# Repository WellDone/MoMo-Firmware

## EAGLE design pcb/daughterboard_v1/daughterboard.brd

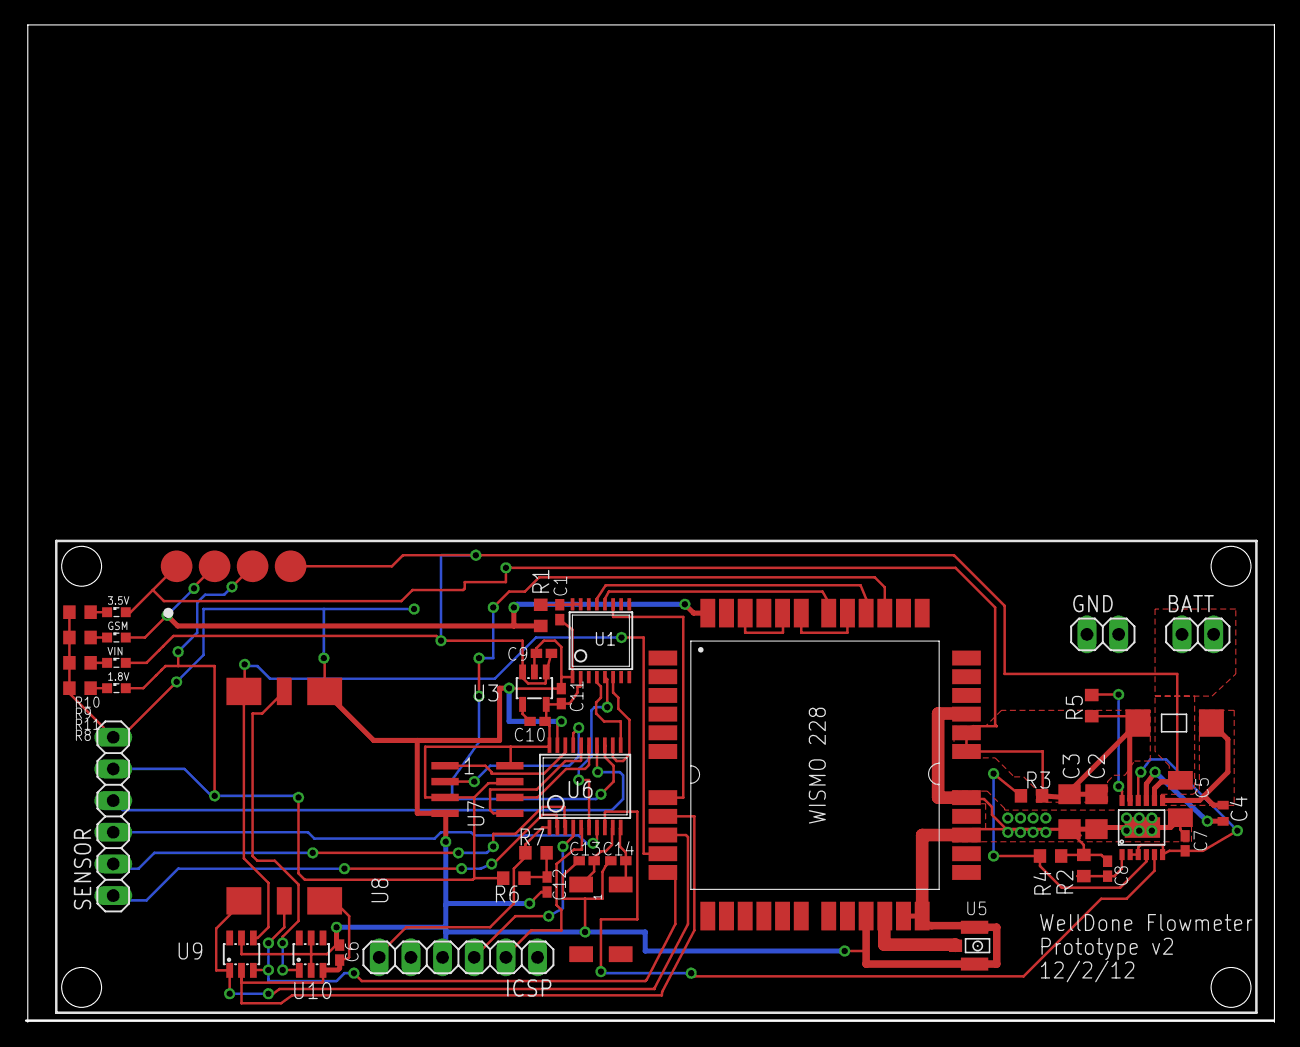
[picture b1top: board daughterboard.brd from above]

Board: 2 copper layers, 100.1 x 80.0 mm, 49 parts (0 on the bottom side), 47 nets.

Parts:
BATT: 1X02
C1: 1 nF; C0402K
C2, C3: 22 uF; C1206
C4: .1 uF; C0402
C5: 22 uF; C1206K
C6: 100 nF; C0402K
C7, C9, C11: 1 uF; C0402K
C8: .1 uF; C0402K
C10: 10 nF; C0402K
C12: .22 uF; C0402K
C13, C14: 3 pF; C0402K
GND: 1X02
ICSP: 1X06
L1: 3.3 uH; INDUCTORPROTO
LED1, LED2, LED3, LED4: SML0603
R1: 200 K; R0603
R2: 70K (1%); R0603
R3: 101K (1%); R0603
R4: 21K (1%); R0603
R5: 101K; R0603
R6: 10K; R0603
R7: 100; R0603
R8: 60; R0603
R9: 600; R0603
R10: 1K; R0603
R11: 2.7K; R0603
SENSOR: 1X06
TP1, TP2, TP3, TP4: TPB2,54; B2,54
U1: LEVELSHIFTER; TSSOP16
U2: LTC3600; MSOP12
U3: LT1761; SOT23-5L
U4: WISMO_228; GSM_MODULE
U5: RFANTENNA; RFJACK
U6: PIC24F16KA101-X_PSSOP; SSOP20
U7: FLASH8MSOP8; SOP08
U8: SIMSLOT
U9: DALC208; SOT23-6L
U10: ESDA6V1SC6; SOT23-6L
XTAL1: 32.768khz; SMDXTAL

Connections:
CLK: U4.SIM_CLK, U8.CLOCK, U9.1
CS: U6.18, U7.1
GND: C1.2, C2.2, C3.2, C5.2, C6.2, C7.2, C8.2, C9.2, C11.2, C12.2, C13.2, C14.2, GND.1, GND.2, ICSP.4, R2.1, R4.1, R8.1, R9.1, R10.1, R11.1, SENSOR.6, U1.1, U2.EXPOSED, U3.2, U4.GND, U4.GND1, U4.GND2, U4.GND3, U4.GND4, U4.GND5, U5.UNUSED1, U5.UNUSED2, U6.19, U7.4, U8.GND, U9.5, U10.2, U10.5
IO: U4.SIM_IO, U8.IO, U9.4
unnamed: U4.ANT, U5.ANTENNA
unnamed: C7.1, U2.PAD2, U2.PAD3, U2.PAD6, U2.PAD10
unnamed: U4.CT107/DSR, U4.CT108/DTR
unnamed: C1.1, R1.1, U1.15, U1.16
unnamed: U8.VPP, U10.1
unnamed: R3.1, R4.2, U2.PAD4
unnamed: LED1.C, R8.2
unnamed: LED2.C, R9.2
unnamed: C4.2, U2.PAD9
unnamed: C8.1, R2.2, U2.PAD1
unnamed: LED3.C, R10.2
unnamed: LED4.C, R11.2
unnamed: U2.PAD5, U6.8
unnamed: R5.1, U2.PAD12
unnamed: ICSP.2, U6.5
unnamed: ICSP.3, U6.4
unnamed: C10.2, U3.4
unnamed: C12.1, R6.1, R7.2
unnamed: ICSP.6, R7.1, U6.1
unnamed: U4.CT105/RTS, U4.CT106/CTS
unnamed: C14.1, U6.10, XTAL1.4
unnamed: C13.1, U6.9, XTAL1.1
unnamed: U1.13, U4.CT103/TXD
unnamed: U1.12, U4.CT104/RXD
unnamed: U1.11, U4.WISMO_READY
ON: U4.ON/OFF, U6.13
P0: SENSOR.1, U6.2
P1: SENSOR.2, U6.3
P2: SENSOR.3, U6.7
P3: SENSOR.4, U6.14
READY: U1.6, U6.12
RESET: U4.SIM_RST, U8.RESET, U9.3
RX: U1.5, U6.6
SCLK: U6.15, U7.6
SDI: U6.17, U7.2
SDO: U6.16, U7.5
SW: C4.1, L1.P1, U2.PAD7
TX: U1.4, U6.11
V+: BATT.1, BATT.2, C5.1, C9.1, LED4.A, TP4.TP, U2.PAD8, U3.1, U3.3
VCCINT: C10.1, C11.1, LED1.A, R6.2, SENSOR.5, TP1.TP, U1.2, U3.5, U6.20, U7.3, U7.7, U7.8
VCCIO: LED2.A, R1.2, TP2.TP, U4.VCC_2V8
VCCSIM: C6.1, U4.SIM_VCC, U8.VCC, U9.2, U10.3
VDD: C2.1, C3.1, L1.P2, LED3.A, R3.2, R5.2, TP3.TP, U2.PAD11, U4.VBAT1, U4.VBAT2

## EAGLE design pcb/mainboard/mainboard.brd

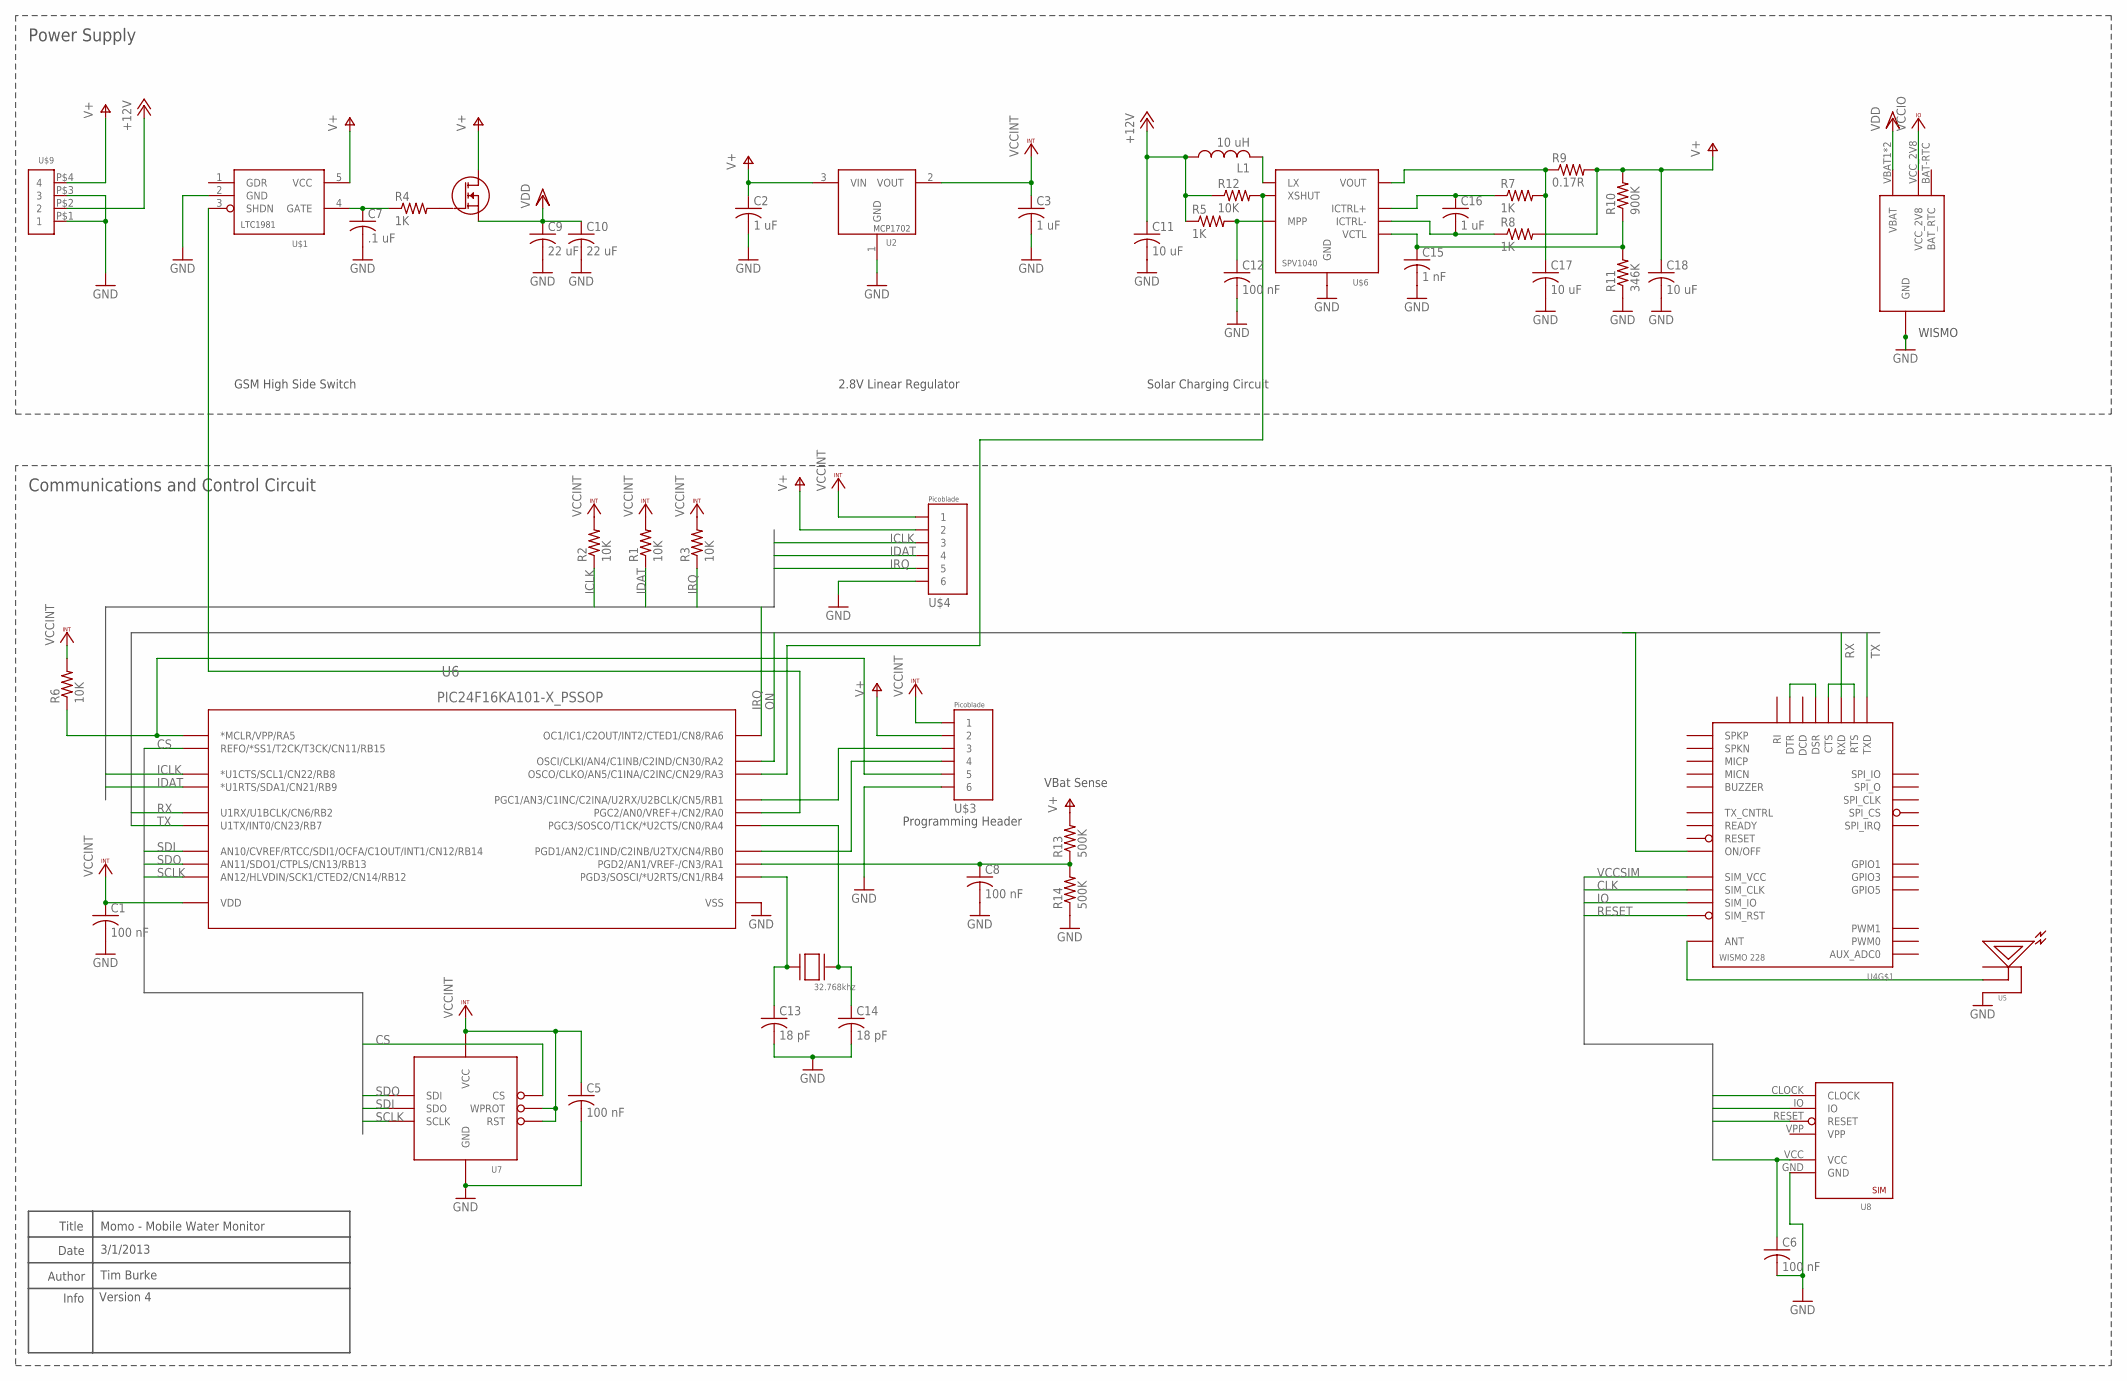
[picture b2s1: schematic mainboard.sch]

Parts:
C1, C5, C8, C12: 100 nF; C0402
C2, C3, C16: 1 uF; C0402
C6: 100 nF; C0402K
C7: .1 uF; C0402
C9, C10: 22 uF; C1206
C11, C17, C18: 10 uF; C0805
C13, C14: 18 pF; C0402K
C15: 1 nF; C0402
L1: 10 uH; L-COILCRAFT
R1, R2, R3, R6, R12: 10K; R0603
R4, R5, R7, R8: 1K; R0603
R9: 0.17R; R0805
R10: 900K; R0603
R11: 346K; R0603
R13, R14: 500K; R0603
U2: MCP1702; SOT23
U4: WISMO_228; GSM_MODULE
U5: RFANTENNA; RFJACK
U6: PIC24F16KA101-X_PSSOP; SSOP20
U7: FLASH8MSOP8; SOP08
U8: SIMSLOT
U$1: LTC1981; SOT23-5L
U$3, U$4: MICROCON6
U$5: N-MOSFET; SSOT-3
U$6: SPV1040; TSSOP8
U$9: SCREWTERM4
XTAL1: 32.768khz; 1206

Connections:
+12V: C11.1, L1.P$1 (1), R5.1, R12.1, U$9.P$2 (2)
CLK: U4.SIM_CLK, U8.CLOCK
CS: U6.18 (REFO/*SS1/T2CK/T3CK/CN11/RB15), U7.1 (CS)
GND: C1.2, C2.2, C3.2, C5.2, C6.2, C7.2, C8.2, C9.2, C10.2, C11.2, C12.2, C13.2, C14.2, C15.2, C17.2, C18.2, R11.1, R14.1, U2.1 (GND), U4.GND, U4.GND1 (GND), U4.GND2 (GND), U4.GND3 (GND), U4.GND4 (GND), U4.GND5 (GND), U5.UNUSED1 (SHIELD), U5.UNUSED2 (SHIELD), U6.19 (VSS), U7.4 (GND), U8.GND, U$1.2 (GND), U$3.6, U$4.6, U$6.2 (GND), U$9.P$1 (1), U$9.P$3 (3)
ICLK: R2.1, U6.12 (*U1CTS/SCL1/CN22/RB8), U$4.3
IDAT: R1.1, U6.13 (*U1RTS/SDA1/CN21/RB9), U$4.4
IO: U4.SIM_IO, U8.IO
IRQ: R3.1, U6.14 (OC1/IC1/C2OUT/INT2/CTED1/CN8/RA6), U$4.5
unnamed: U4.ANT, U5.ANTENNA (PIN)
unnamed: U4.CT107/DSR (DSR), U4.CT108/DTR (DTR)
unnamed: R4.2, U$5.1 (GATE)
unnamed: C12.1, R5.2, U$6.1 (MPP)
unnamed: C7.1, R4.1, U$1.4 (GATE)
unnamed: U6.2 (PGC2/AN0/VREF+/CN2/RA0), U$1.3 (SHDN)
unnamed: L1.P$2 (2), U$6.3 (LX)
unnamed: C15.1, R10.1, R11.2, U$6.5 (VCTL)
unnamed: C17.1, R7.2, R9.1, U$6.4 (VOUT)
unnamed: C16.1, R7.1, U$6.7 (ICTRL+)
unnamed: C16.2, R8.1, U$6.6 (ICTRL-)
unnamed: R12.2, U6.8 (OSCO/CLKO/AN5/C1INA/C2INC/CN29/RA3), U$6.8 (XSHUT)
unnamed: R6.1, U6.1 (*MCLR/VPP/RA5), U$3.5
unnamed: C8.1, R13.1, R14.2, U6.3 (PGD2/AN1/VREF-/CN3/RA1)
unnamed: U6.5 (PGC1/AN3/C1INC/C2INA/U2RX/U2BCLK/CN5/RB1), U$3.3
unnamed: U6.4 (PGD1/AN2/C1IND/C2INB/U2TX/CN4/RB0), U$3.4
unnamed: U4.CT105/RTS (RTS), U4.CT106/CTS (CTS)
unnamed: C14.1, U6.10 (PGC3/SOSCO/T1CK/*U2CTS/CN0/RA4), XTAL1.P$2 (XTAL2)
unnamed: C13.1, U6.9 (PGD3/SOSCI/*U2RTS/CN1/RB4), XTAL1.P$1 (XTAL1)
ON: U4.ON/OFF, U6.7 (OSCI/CLKI/AN4/C1INB/C2IND/CN30/RA2)
RESET: U4.SIM_RST, U8.RESET
RX: U4.CT104/RXD (RXD), U6.6 (U1RX/U1BCLK/CN6/RB2)
SCLK: U6.15 (AN12/HLVDIN/SCK1/CTED2/CN14/RB12), U7.6 (SCLK)
SDI: U6.17 (AN10/CVREF/RTCC/SDI1/OCFA/C1OUT/INT1/CN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), U7.2 (SDO)
SDO: U6.16 (AN11/SDO1/CTPLS/CN13/RB13), U7.5 (SDI)
TX: U4.CT103/TXD (TXD), U6.11 (U1TX/INT0/CN23/RB7)
V+: C2.1, C18.1, R8.2, R9.2, R10.2, R13.2, U2.3 (VIN), U$1.5 (VCC), U$3.2, U$4.2, U$5.3 (DRAIN), U$9.P$4 (4)
VCCINT: C1.1, C3.1, C5.1, R1.2, R2.2, R3.2, R6.2, U2.2 (VOUT), U6.20 (VDD), U7.3 (WPROT), U7.7 (RST), U7.8 (VCC), U$3.1, U$4.1
VCCIO: U4.VCC_2V8
VCCSIM: C6.1, U4.SIM_VCC, U8.VCC
VDD: C9.1, C10.1, U4.VBAT1 (VBAT), U4.VBAT2 (VBAT), U$5.2 (SOURCE)

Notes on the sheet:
WISMO
Programming Header
Communications and Control Circuit
Power Supply
GSM High Side Switch
2.8V Linear Regulator
Title
Author
Date
Momo - Mobile Water Monitor
3/1/2013
Tim Burke
Info
Version 4
Solar Charging Circuit
VBat Sense

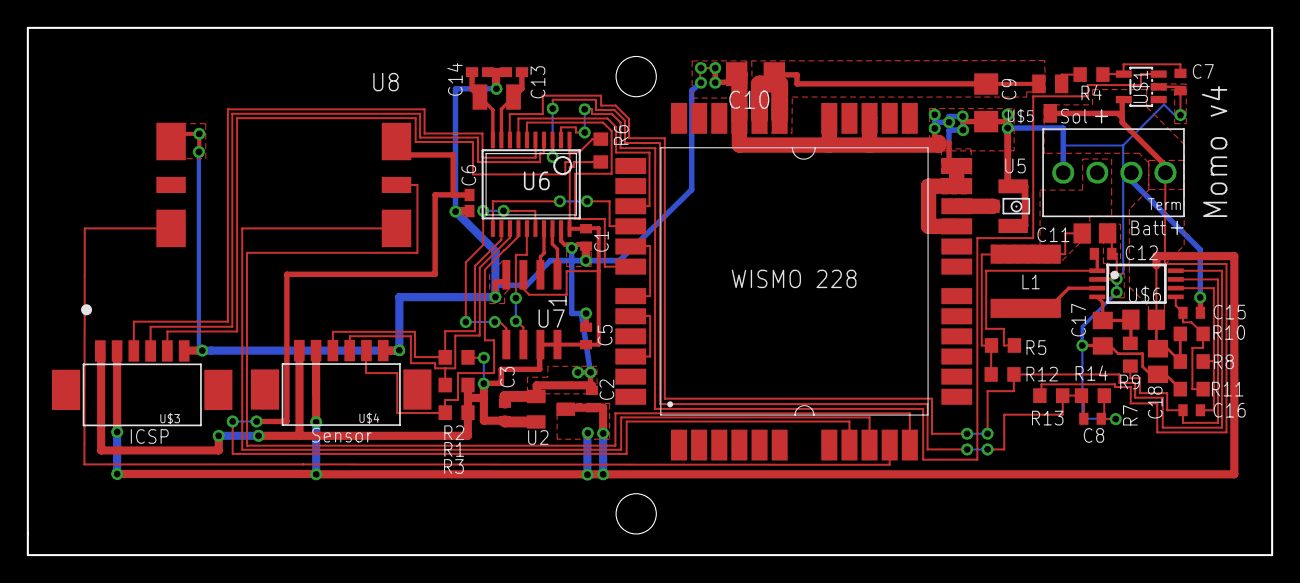
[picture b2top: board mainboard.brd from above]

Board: 2 copper layers, 92.7 x 39.3 mm, 45 parts (0 on the bottom side), 38 nets.

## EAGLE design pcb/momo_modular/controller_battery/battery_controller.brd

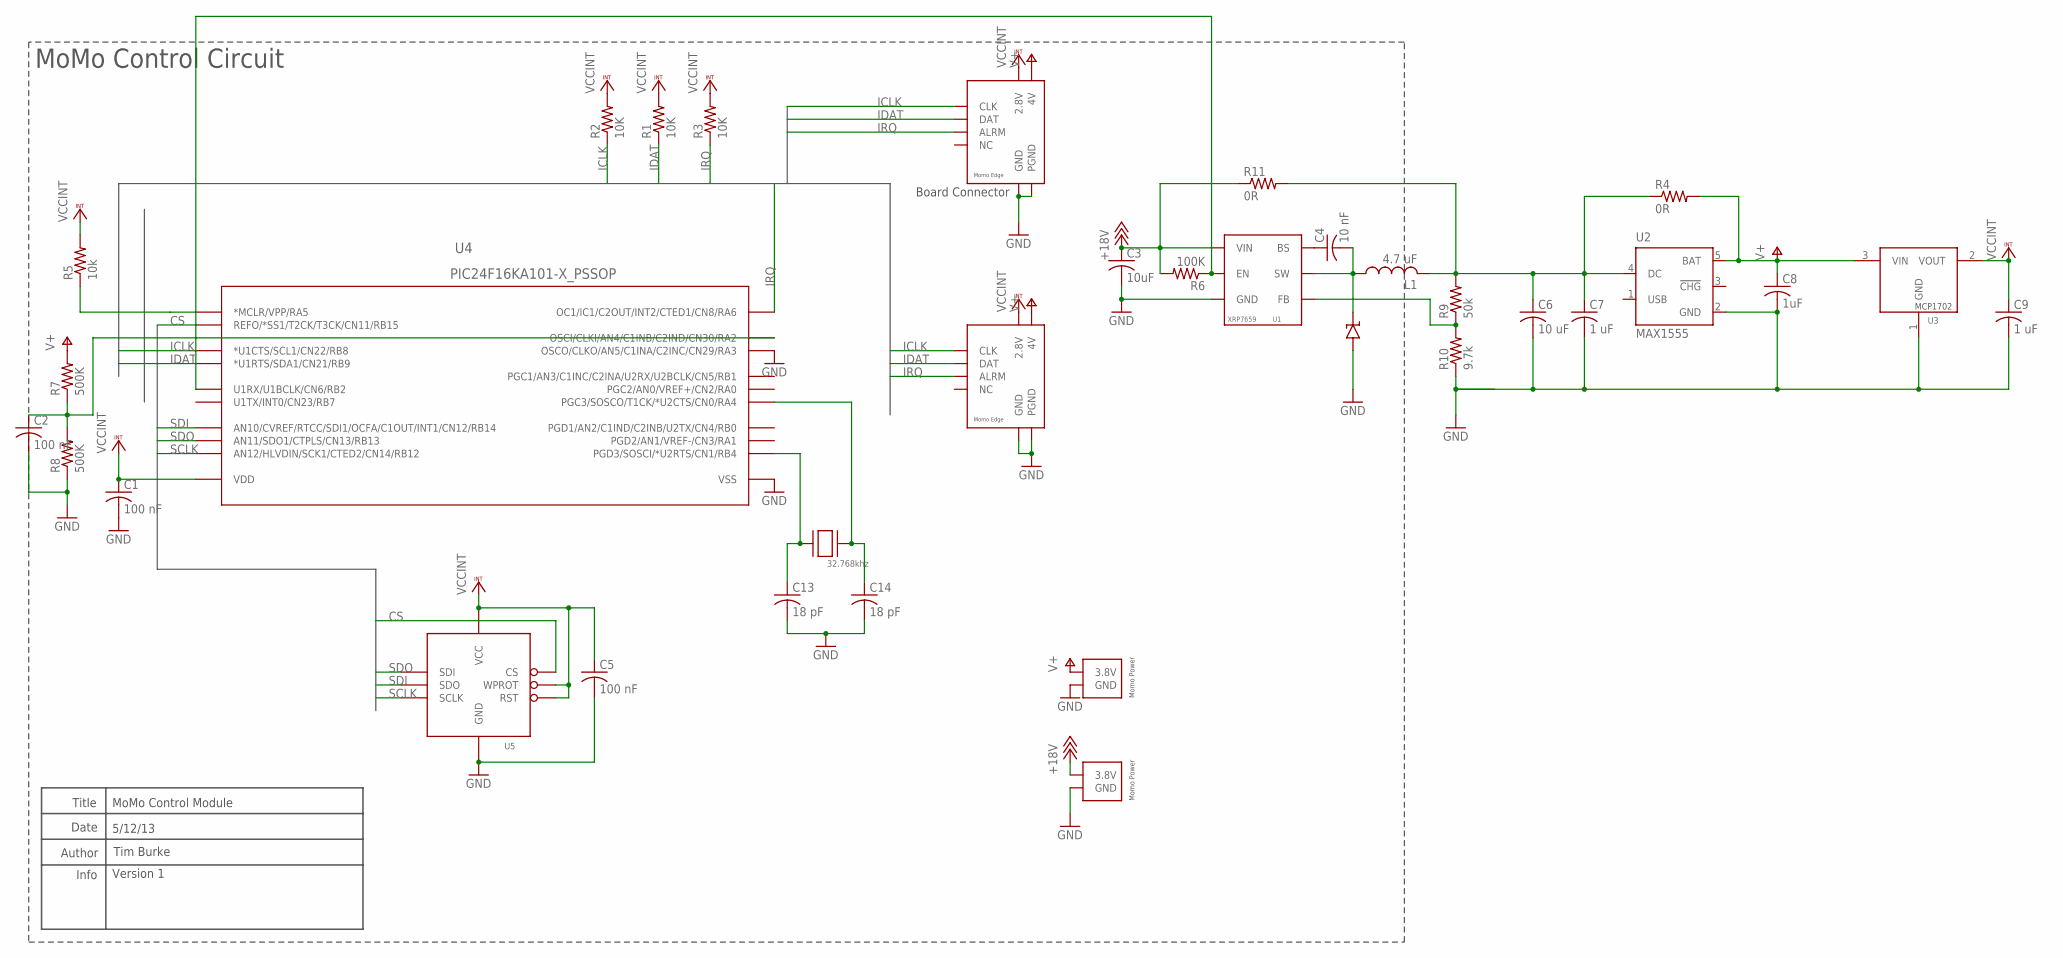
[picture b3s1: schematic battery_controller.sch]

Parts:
C1, C2, C5: 100 nF; C0402
C3: 10uF; C0805
C4: 10 nF; C0402
C6: 10 uF; C0805
C7, C9: 1 uF; C0402
C8: 1uF; C0402
C13, C14: 18 pF; C0402K
D1: DIODE_SS2P3SS2P3; DIODE_SS2P3
JP1: MOMO-VERT-8M; 1X08
JP3: MOMO-EDGE-8F
L1: 4.7 uF; NR6028-INDUCTOR
R1, R2, R3: 10K; R0603
R4, R11: 0R; R0603
R5: 10k; R0402
R6: 100K; R0603
R7, R8: 500K; R0603
R9: 50k; R0603
R10: 9.7k; R0603
U1: XRP7659; SOT23-6L
U2: MAX1555; SOT23-5L
U3: MCP1702; SOT23
U4: PIC24F16KA101-X_PSSOP; SSOP20
U5: FLASH8MSOP8; SOP08
U$1, U$2: MOMO-EDGE-POWER-M; MOMO-EDGE-SMALL-2M
XTAL1: 32.768khz; 1206

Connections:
+18V: C3.1, R6.2, R11.1, U1.5 (VIN), U$1.2 (3.8V)
CS: U4.18 (REFO/*SS1/T2CK/T3CK/CN11/RB15), U5.1 (CS)
GND: C1.2, C2.2, C3.2, C5.2, C6.2, C7.2, C8.2, C9.2, C13.2, C14.2, D1.AN, JP1.6 (GND), JP1.8 (PGND), JP3.GND, JP3.PGND, R8.1, R10.1, U1.2 (GND), U2.2 (GND), U3.1 (GND), U4.8 (OSCO/CLKO/AN5/C1INA/C2INC/CN29/RA3), U4.19 (VSS), U5.4 (GND), U$1.1 (GND), U$2.1 (GND)
ICLK: JP1.3 (CLK), JP3.CLK, R2.1, U4.12 (*U1CTS/SCL1/CN22/RB8)
IDAT: JP1.4 (DAT), JP3.DAT, R1.1, U4.13 (*U1RTS/SDA1/CN21/RB9)
IRQ: JP1.5 (ALRM), JP3.ARLM (ALRM), R3.1, U4.14 (OC1/IC1/C2OUT/INT2/CTED1/CN8/RA6)
unnamed: C6.1, C7.1, L1.2, R4.1, R9.2, R11.2, U2.4 (DC)
unnamed: C2.1, R7.1, R8.2, U4.7 (OSCI/CLKI/AN4/C1INB/C2IND/CN30/RA2)
unnamed: R6.1, U1.4 (EN), U4.6 (U1RX/U1BCLK/CN6/RB2)
unnamed: R9.1, R10.2, U1.3 (FB)
unnamed: C4.1, U1.1 (BS)
unnamed: C4.2, D1.CATH, L1.1, U1.6 (SW)
unnamed: R5.1, U4.1 (*MCLR/VPP/RA5)
unnamed: C14.1, U4.10 (PGC3/SOSCO/T1CK/*U2CTS/CN0/RA4), XTAL1.P$2 (XTAL2)
unnamed: C13.1, U4.9 (PGD3/SOSCI/*U2RTS/CN1/RB4), XTAL1.P$1 (XTAL1)
SCLK: U4.15 (AN12/HLVDIN/SCK1/CTED2/CN14/RB12), U5.6 (SCLK)
SDI: U4.17 (AN10/CVREF/RTCC/SDI1/OCFA/C1OUT/INT1/CN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), U5.2 (SDO)
SDO: U4.16 (AN11/SDO1/CTPLS/CN13/RB13), U5.5 (SDI)
V+: C8.1, JP1.7 (4V), JP3.V4. (4V), R4.2, R7.2, U2.5 (BAT), U3.3 (VIN), U$2.2 (3.8V)
VCCINT: C1.1, C5.1, C9.1, JP1.1 (2.8V), JP3.V28 (2.8V), R1.2, R2.2, R3.2, R5.2, U3.2 (VOUT), U4.20 (VDD), U5.3 (WPROT), U5.7 (RST), U5.8 (VCC)

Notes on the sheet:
Title
Author
Date
Tim Burke
Info
Board Connector
MoMo Control Module
Version 1
5/12/13
MoMo Control Circuit

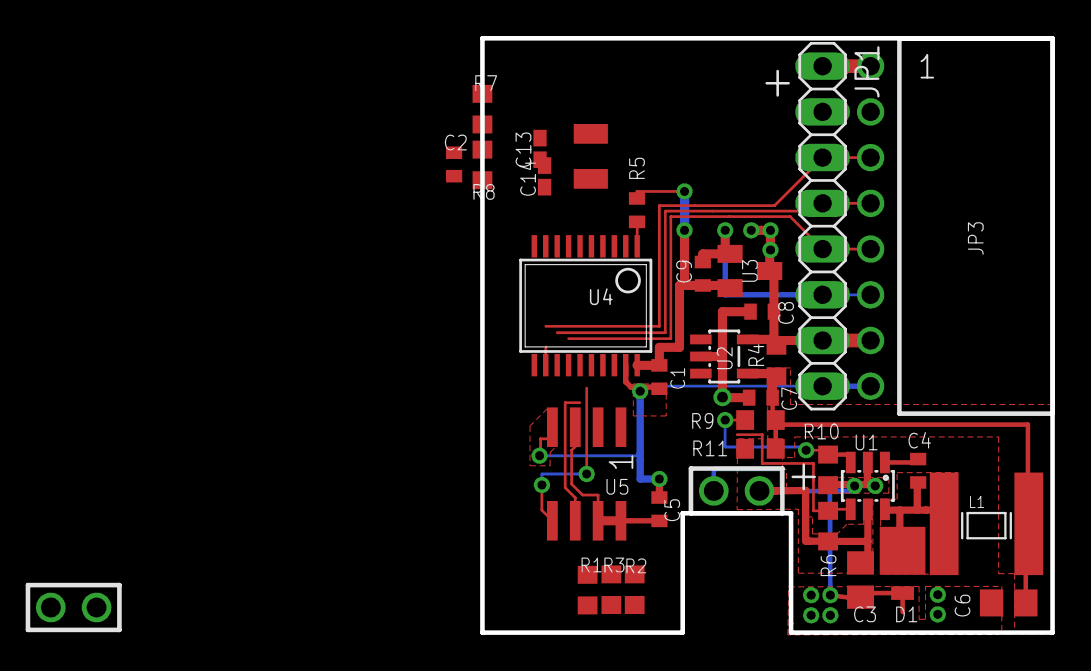
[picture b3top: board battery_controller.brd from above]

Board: 2 copper layers, 31.7 x 33.0 mm, 34 parts (0 on the bottom side), 20 nets.

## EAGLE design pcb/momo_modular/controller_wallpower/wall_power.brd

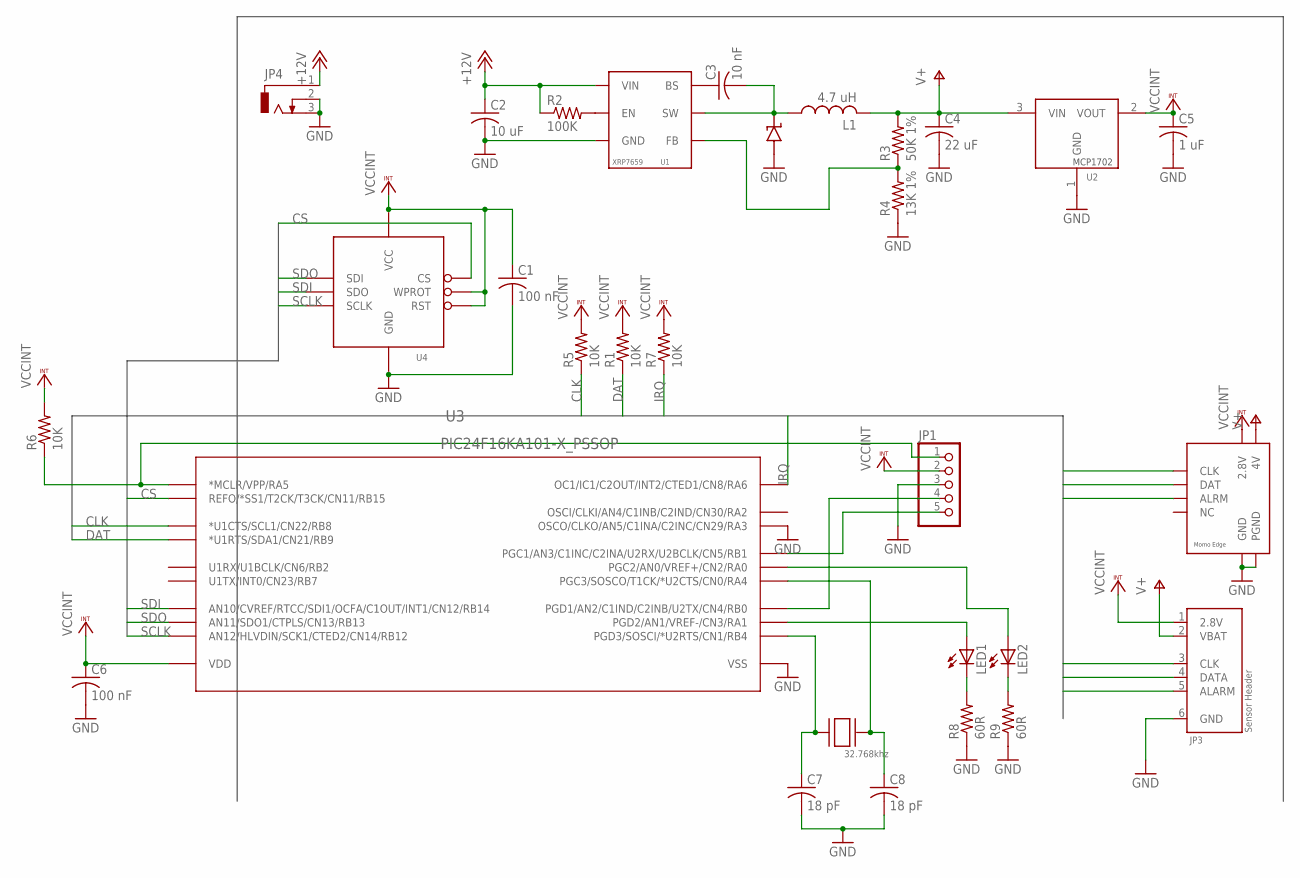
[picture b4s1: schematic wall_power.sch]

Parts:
C1, C6: 100 nF; C0402
C2: 10 uF; C0805
C3: 10 nF; C0402
C4: 22 uF; C1206
C5: 1 uF; C0402
C7, C8: 18 pF; C0402K
D1: DIODE_SS2P3SS2P3; DIODE_SS2P3
JP1: PINHD-1X5; 1X05
JP2: MOMO-EDGE-8F
JP3: MOMO-SENSOR-HEADER; 2X3-MOLEX-90130
JP4: DCJ0303
L1: 4.7 uH; NR6028-INDUCTOR
LED1, LED2: LEDSML0603; SML0603
R1, R5, R6, R7: 10K; R0603
R2: 100K; R0603
R3: 50K 1%; R0603
R4: 13K 1%; R0603
R8, R9: 60R; R0603
U1: XRP7659; SOT23-6L
U2: MCP1702; SOT23
U3: PIC24F16KA101-X_PSSOP; SSOP20
U4: FLASH8MSOP8; SOP08
XTAL1: 32.768khz; 1206

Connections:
+12V: C2.1, JP4.1, R2.1, U1.5 (VIN)
CLK: JP2.CLK, JP3.3 (CLK), R5.1, U3.12 (*U1CTS/SCL1/CN22/RB8)
CS: U3.18 (REFO/*SS1/T2CK/T3CK/CN11/RB15), U4.1 (CS)
DAT: JP2.DAT, JP3.4 (DATA), R1.1, U3.13 (*U1RTS/SDA1/CN21/RB9)
GND: C1.2, C2.2, C4.2, C5.2, C6.2, C7.2, C8.2, D1.AN, JP1.3, JP2.GND, JP2.PGND, JP3.6 (GND), JP4.2, JP4.3, R4.1, R8.1, R9.1, U1.2 (GND), U2.1 (GND), U3.8 (OSCO/CLKO/AN5/C1INA/C2INC/CN29/RA3), U3.19 (VSS), U4.4 (GND)
IRQ: JP2.ARLM (ALRM), JP3.5 (ALARM), R7.1, U3.14 (OC1/IC1/C2OUT/INT2/CTED1/CN8/RA6)
unnamed: LED2.A, U3.2 (PGC2/AN0/VREF+/CN2/RA0)
unnamed: C3.2, D1.CATH, L1.1, U1.6 (SW)
unnamed: R2.2, U1.4 (EN)
unnamed: C3.1, U1.1 (BS)
unnamed: LED2.C, R9.2
unnamed: R3.1, R4.2, U1.3 (FB)
unnamed: LED1.C, R8.2
unnamed: LED1.A, U3.3 (PGD2/AN1/VREF-/CN3/RA1)
unnamed: JP1.4, U3.4 (PGD1/AN2/C1IND/C2INB/U2TX/CN4/RB0)
unnamed: JP1.5, U3.5 (PGC1/AN3/C1INC/C2INA/U2RX/U2BCLK/CN5/RB1)
unnamed: JP1.1, R6.1, U3.1 (*MCLR/VPP/RA5)
unnamed: C8.1, U3.10 (PGC3/SOSCO/T1CK/*U2CTS/CN0/RA4), XTAL1.P$2 (XTAL2)
unnamed: C7.1, U3.9 (PGD3/SOSCI/*U2RTS/CN1/RB4), XTAL1.P$1 (XTAL1)
SCLK: U3.15 (AN12/HLVDIN/SCK1/CTED2/CN14/RB12), U4.6 (SCLK)
SDI: U3.17 (AN10/CVREF/RTCC/SDI1/OCFA/C1OUT/INT1/CN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), U4.2 (SDO)
SDO: U3.16 (AN11/SDO1/CTPLS/CN13/RB13), U4.5 (SDI)
V+: C4.1, JP2.V4. (4V), JP3.2 (VBAT), L1.2, R3.2, U2.3 (VIN)
VCCINT: C1.1, C5.1, C6.1, JP1.2, JP2.V28 (2.8V), JP3.1 (2.8V), R1.2, R5.2, R6.2, R7.2, U2.2 (VOUT), U3.20 (VDD), U4.3 (WPROT), U4.7 (RST), U4.8 (VCC)

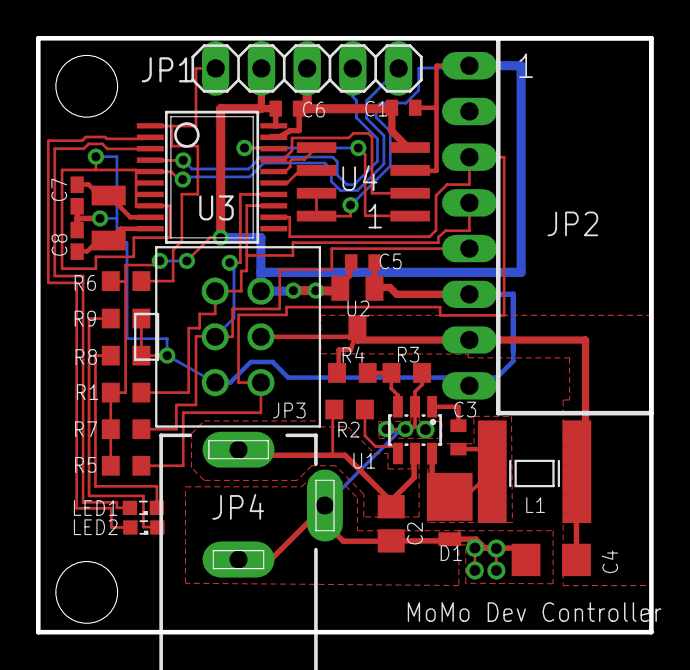
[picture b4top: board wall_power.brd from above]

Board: 2 copper layers, 34.1 x 33.0 mm, 30 parts (0 on the bottom side), 24 nets.

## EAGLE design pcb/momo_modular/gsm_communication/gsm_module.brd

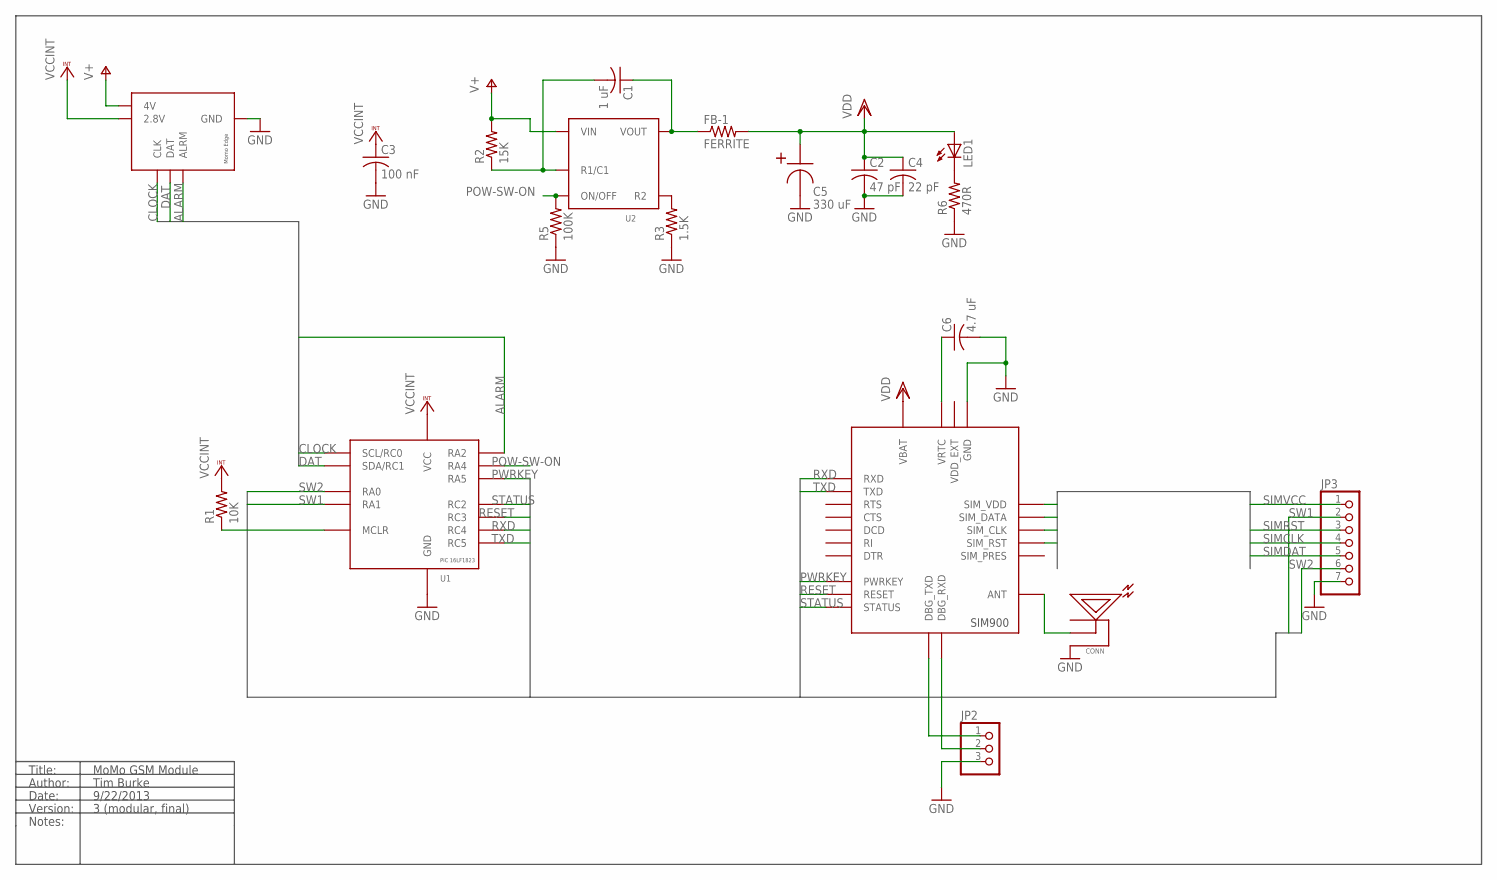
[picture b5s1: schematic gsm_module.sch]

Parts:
C1: 1 uF; C0402K; DIGIKEY-PN 445-4114-1-ND
C2: 47 pF; C0402K; DIGIKEY-PN 445-1243-1-ND
C3: 100 nF; C0402; DIGIKEY-PN 445-1265-1-ND
C4: 22 pF; C0402K; DIGIKEY-PN 445-1239-1-ND
C5: 330 uF; 2917
C6: 4.7 uF; C0805; DIGIKEY-PN 1276-1259-1-ND
CONN: RFANTENNA; RFJACK; DIGIKEY-PN J983CT-ND
FB-1: FERRITE; R0805; DIGIKEY-PN 445-1567-1-ND
JP1: MOMO-EDGE-6M
JP2: PINHD-1X3; 1X03
JP3: PINHD-1X7; 1X07
LED1: LEDCHIPLED_0603; CHIPLED_0603; DIGIKEY-PN 475-2709-1-ND
R1: 10K; R0603; DIGIKEY-PN P10.0KHCT-ND
R2: 15K; R0603; DIGIKEY-PN P15KGCT-ND
R3: 1.5K; R0603; DIGIKEY-PN P1.5KGCT-ND
R5: 100K; R0603; DIGIKEY-PN P100KHCT-ND
R6: 470R; R0603
U1: PIC16LF1823; SO14; DIGIKEY-PN PIC16LF1823-I/SL-ND
U2: TI-HIGHSIDE-PFET; SOT23-6L
U3: SIM900

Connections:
ALARM: JP1.ALARM (ALRM), U1.11 (RA2)
CLOCK: JP1.CLK, U1.10 (SCL/RC0)
DAT: JP1.DAT, U1.9 (SDA/RC1)
DEBUGRX: JP2.2, U3.28 (DBG_RXD)
DEBUGTX: JP2.1, U3.27 (DBG_TXD)
GND: C2.2, C3.2, C4.2, C5.-, C6.2, CONN.UNUSED1 (SHIELD), CONN.UNUSED2 (SHIELD), JP1.GND, JP2.3, JP3.7, R3.1, R5.1, R6.1, U1.14 (GND), U3.17 (GND), U3.18 (GND), U3.29 (GND), U3.39 (GND), U3.45 (GND), U3.46 (GND), U3.53 (GND), U3.54 (GND), U3.58 (GND), U3.59 (GND), U3.61 (GND), U3.62 (GND), U3.63 (GND), U3.64 (GND), U3.65 (GND)
unnamed: R3.2, U2.1 (R2)
unnamed: LED1.C, R6.2
unnamed: C1.2, R2.1, U2.6 (R1/C1)
unnamed: C1.1, FB-1.1, U2.2 (VOUT), U2.3 (VOUT)
unnamed: C6.1, U3.26 (VRTC)
unnamed: R1.1, U1.4 (MCLR)
unnamed: CONN.ANTENNA (PIN), U3.60 (ANT)
POW-SW-ON: R5.2, U1.3 (RA4), U2.5 (ON/OFF)
PWRKEY: U1.2 (RA5), U3.1 (PWRKEY)
RESET: U1.7 (RC3), U3.16 (RESET)
RXD: U1.6 (RC4), U3.10 (RXD)
SIMCLK: JP3.4, U3.32 (SIM_CLK)
SIMDAT: JP3.5, U3.31 (SIM_DATA)
SIMRST: JP3.3, U3.33 (SIM_RST)
SIMVCC: JP3.1, U3.30 (SIM_VDD)
STATUS: U1.8 (RC2), U3.66 (STATUS)
SW1: JP3.2, U1.12 (RA1)
SW2: JP3.6, U1.13 (RA0)
TXD: U1.5 (RC5), U3.9 (TXD)
V+: JP1.4V, R2.2, U2.4 (VIN)
VCCINT: C3.1, JP1.V28 (2.8V), R1.2, U1.1 (VCC)
VDD: C2.1, C4.1, C5.+, FB-1.2, LED1.A, U3.55 (VBAT), U3.56 (VBAT), U3.57 (VBAT)
VDD_EXT: U3.15 (VDD_EXT)

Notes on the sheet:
Title:
Author:
Date:
Version:
Notes:
MoMo GSM Module
Tim Burke
9/22/2013
3 (modular, final)

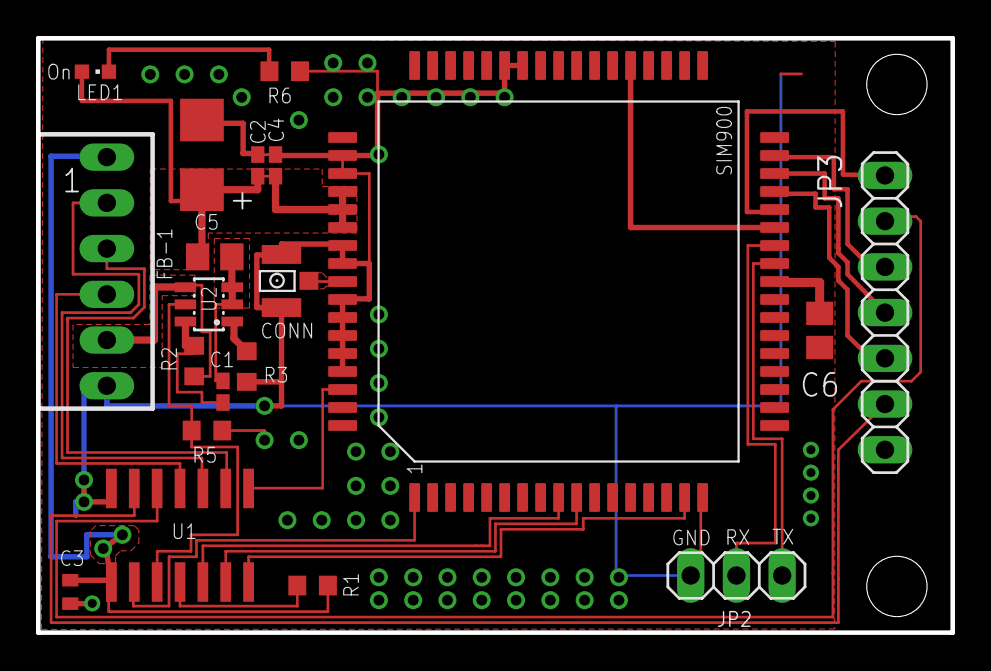
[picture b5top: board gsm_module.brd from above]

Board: 2 copper layers, 50.8 x 33.0 mm, 20 parts (0 on the bottom side), 28 nets.

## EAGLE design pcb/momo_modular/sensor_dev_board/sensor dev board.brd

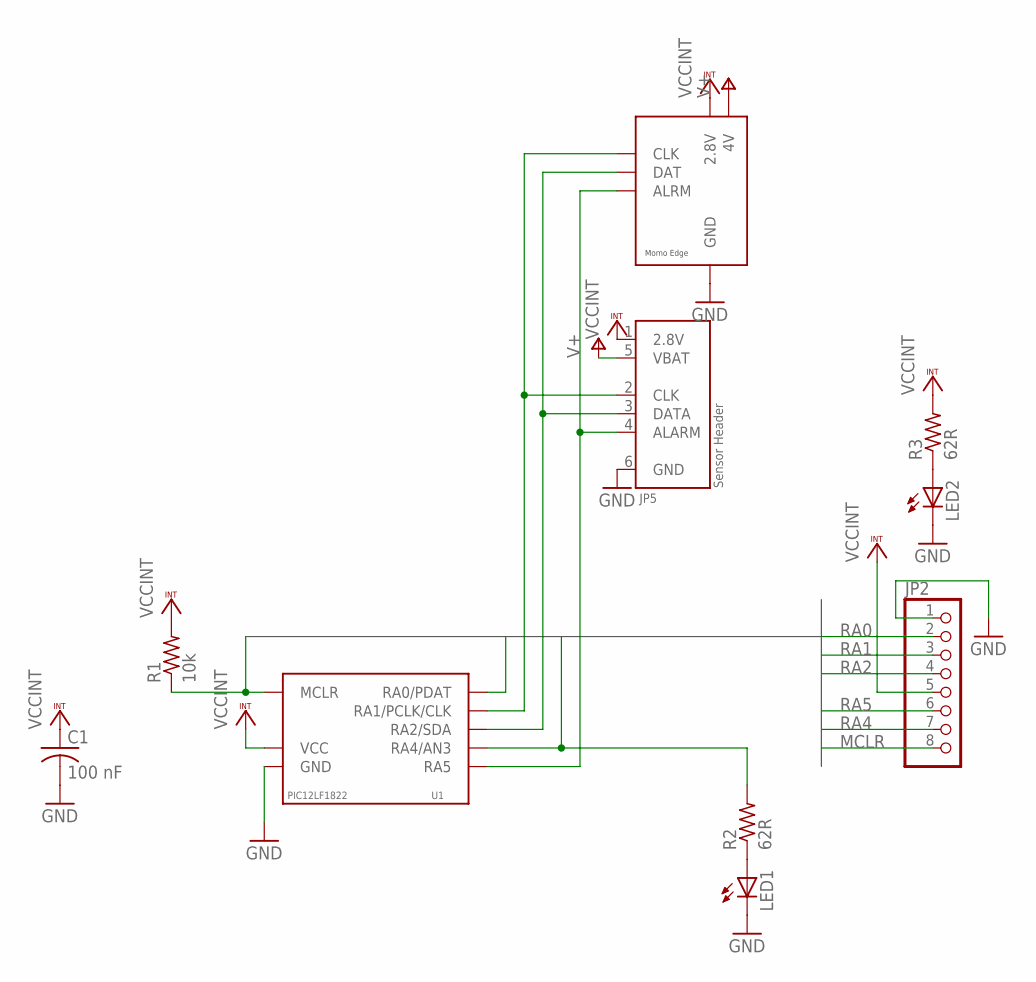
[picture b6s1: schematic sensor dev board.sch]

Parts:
C1: 100 nF; C0402; DIGIKEY-PN 445-1265-1-ND
JP2: PINHD-1X8; 1X08; DIGIKEY-PN S1012EC-08-ND
JP4: MOMO-VERT-6M; 1X06; DIGIKEY-PN S7004-ND
JP5: MOMO-SENSOR-RJ11; RJ-12
LED1, LED2: LEDCHIP-LED0603; CHIP-LED0603; DIGIKEY-PN 475-2709-1-ND
R1: 10k; R0603; DIGIKEY-PN P10.0KHCT-ND
R2, R3: 62R; R0603; DIGIKEY-PN P62GCT-ND
U1: PIC12LF1822; SOIC8; DIGIKEY-PN PIC12LF1822-I/SN

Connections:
GND: C1.2, JP2.1, JP4.7 (GND), JP5.6 (GND), LED1.C, LED2.C, U1.8 (GND)
MCLR: JP2.8, R1.1, U1.4 (MCLR)
unnamed: LED1.A, R2.1
unnamed: LED2.A, R3.1
RA0: JP2.2, U1.7 (RA0/PDAT)
RA1: JP2.3, JP4.3 (CLK), JP5.2 (CLK), U1.6 (RA1/PCLK/CLK)
RA2: JP2.4, JP4.4 (DAT), JP5.3 (DATA), U1.5 (RA2/SDA)
RA4: JP2.7, R2.2, U1.3 (RA4/AN3)
RA5: JP2.6, JP4.5 (ALRM), JP5.4 (ALARM), U1.2 (RA5)
V+: JP4.6 (4V), JP5.5 (VBAT)
VCCINT: C1.1, JP2.5, JP4.1 (2.8V), JP5.1 (2.8V), R1.2, R3.2, U1.1 (VCC)

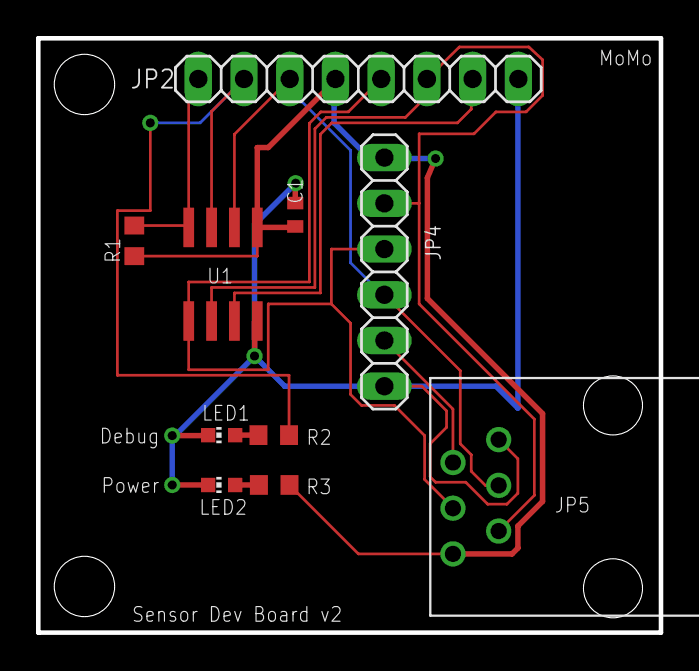
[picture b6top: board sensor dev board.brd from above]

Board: 2 copper layers, 34.6 x 33.0 mm, 10 parts (0 on the bottom side), 11 nets.

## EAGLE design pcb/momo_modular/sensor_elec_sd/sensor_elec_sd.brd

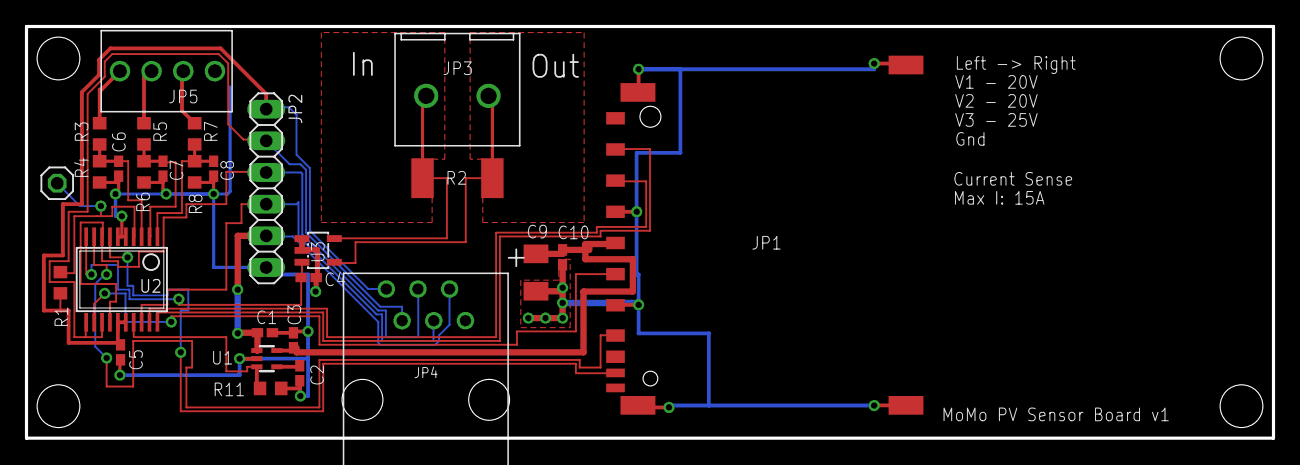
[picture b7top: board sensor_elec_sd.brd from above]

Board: 2 copper layers, 100.0 x 33.0 mm, 28 parts (0 on the bottom side), 24 nets.

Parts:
C1, C3: 1 uF; C0402K
C2, C5, C6, C7, C8, C10: 100 nF; C0402K
C4: 47 nF; C0402K
C9: 22 uF; C1206K
JP1: SDCARD-HOLDER; SDHOLDER-9PIN
JP2: MOMO-VERT-6M; 1X06
JP3: 5MM-SCREWTERM-2POS; 5MM-SCREWTERM
JP4: MOMO-SENSOR-RJ11; RJ-12
JP5: SCREWTERM4
JP6: 1X01
R1: 10K; R0603
R2: 0.001R; R2512
R3, R5: 620K 1%; R0603
R4, R6, R8: 100K 1%; R0603
R7: 806K 1%; R0603
R11: 100K; R0603
U1: AP7115-LDO; SOT353
U2: 16LF1847; SSOP20
U3: TS1100; SOT23-5L

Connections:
ALARM: JP2.5, JP4.4, U2.18
CDET: JP1.CDETECT, U2.7
CS: JP1.1, U2.20
GND: C1.2, C2.2, C3.2, C4.2, C5.2, C6.2, C7.2, C8.2, C9.2, C10.2, JP1.3, JP1.6, JP1.CDGND, JP1.CDGND_BOT, JP1.WPGND, JP1.WPGND_BOT, JP2.7, JP4.6, JP5.P$4, R4.1, R6.1, R8.1, R11.1, U1.2, U2.5, U2.6, U3.1, U3.2
ISENSE: C4.1, U2.10, U3.3
unnamed: C2.1, U1.4
unnamed: JP6.1, R1.1, U2.4
unnamed: JP5.P$1, R3.2
unnamed: JP5.P$2, R5.2
unnamed: JP5.P$3, R7.2
REG_EN: R11.2, U1.3, U2.17
RS+: JP3.P$2, R2.2, U3.5
RS-: JP3.P$1, R2.1, U3.4
SCK: JP1.5, U2.12
SCL: JP2.3, JP4.2, U2.11, U2.13
SD0: JP1.2, U2.19
SDA: JP2.4, JP4.3, U2.8, U2.14
SDI: JP1.7, U2.9
V1: C6.1, R3.1, R4.2, U2.3
V2: C7.1, R5.1, R6.2, U2.2
V3: C8.1, R7.1, R8.2, U2.1
V+: C1.1, JP2.6, JP4.5, U1.1
VCCINT: C5.1, JP2.1, JP4.1, R1.2, U2.15, U2.16
VCCIO: C3.1, C9.1, C10.1, JP1.4, U1.5
